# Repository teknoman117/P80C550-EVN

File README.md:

P80C550-EVN (Rev 1.01)
====================

The P80C550-EVN is a small 8051 single board computer designed around the notion of sourcing the major components from the random collection of electronics I've accumulated over the years. It started as a breadboard computer I built after being inspired to resume my electronics hobby after watching Ben Eater's YouTube series. After carting the breadboard computer around enough for the wires to start randomly loosening, I figured I might as well make a proper PCB for the project.

Features
--------
- CPU: P80C550 @ 11.0592 MHz
- 32 KiB ROM
- 32 KiB SRAM
- Expansion Bus
- HD44780 LCD connector
- 8x 8 bit ADC channels (from CPU)
- AM85C30 Dual UART or SDLC controller
- PCF8584 I2C controller
- MC146818 RTC and RAM with battery backup
- Runs off 5V, or 7V to 18V
- Configurable battery saver with CPU interrupt

Revision History
----------------
Revision 1.0
  - First Board Produced
  - Design and/or Production Errors
    - MAX693 RST signal (active-high) is open collector. This was not mentioned in the chip's datasheet, therefore no pull-up was designed into the board. [#1](https://github.com/teknoman117/P80C550-EVN/issues/1)
    - MAX693 ~RST signal (active-low, wired-OR) does not propagate to RST (active-high). Pushing the reset button will reset only the peripherals and not the CPU. [#2](https://github.com/teknoman117/P80C550-EVN/issues/2)

Revision 1.01
  - Disconnects the non-inverted RST signal from the MAX693
  - Add BSS84 P-Channel MOSFET to invert the ~RST signal. The P80C550 has an internal 50k to 300k pulldown resistor and the ~RST signal is current limited, so no additional components are required other than the MOSFET.

The Hardware
============

## Processor

The CPU is a ROM-less CMOS 8051 microcontroller made by Signetics in the late 1980's. The only major differences from the original are that the Signetics part integrates an 8 bit analog to digital converter (with an 8 channel mux on Port 1), a programmable watchdog timer, and is built on a CMOS process. By nature of being ROM-less, the majority of the I/O ports must be used for the external bus interface (Port 2 = A8..15, Port 0 = AD0..7, Port 3.6 and 3.7 are the ~RD and ~WR signals). This is both good and bad, as we must use extra chips to get GPIO functions, but allows us to use far more than the 2K/4K/8K of ROM the 8051 could be ordered with and the 128 bytes of internal RAM. You can also use EEPROM or Flash for code storage, which is much nicer than needing to pick up an EPROM eraser.

## Memory Map

The memory for the board is provided via two 28 pin JEDEC compliant memory sockets supporting up to 32 KiB each. The left socket is for the ROM and the right socket is for the external data memory. Typically, an SRAM would be installed into the data socket, but this could also be a ROM or Flash device (such as AT29Cxx) if memory beyond the 128 byte internal RAM and 50 byte RTC/CMOS RAM is not required. Both sockets are mapped in the lower half of their respective address spaces (ROM in lower 32 KiB of CODE memory and the RAM in the lower 32 KiB of XDATA memory).

The onboard peripherals are mapped in the 8 KiB of address space following the XDATA memory as 1 KiB chunks. This may seem wasteful, but it allows using a single '138 3-to-8 decoder for peripheral chip selects (active high enable is A15, active low enables are A14 and A13. A12 -> A10 are then used for the select input).

| Code Address   | Description |
| -------------- | ----------- |
| 0000h -> 7FFFh | 32 KiB ROM socket (by default - see [Expansion](#expansion)) |
| 8000h -> FFFFh | **unused**  |

| Data Address   | Description                                     |
| -------------- | ----------------------------------------------- |
| 0000h -> 7FFFh | 32 KiB XDATA socket                             |
| 8000h          | [Power Status Register](#power-status-register) |
| 8400h -> 8FFFh | **unused**                                      |
| 9000h -> 903Fh | [RTC](#rtc)                                     |
| 9400h -> 9403h | [UART / SDLC](#uart--sdlc)                      |
| 9800h -> 9801h | [I2C controller](#i2c)                          |
| 9C00h -> 9C01h | [LCD](#lcd)                                     |
| A000h -> FFFFh | **unused**                                      |

## Interrupts

The P80C550 has two external interrupt lines which can either be falling edge triggered or low level triggered. There is an internal pullup resistor on the CPU and peripherals with open collector interrupt outputs can be wire-OR'd together on the same interrupt line.

| Interrupt | Devices                |
| --------- | ---------------------- |
| EX0       | Power Fault, RTC, I2C  |
| EX1       | UART / SDLC            |

## Power and Battery Saver

The board can either be powered directly via the 5V rail, or by a 7V to 18V terminal block, which is regulated to 5V by an AP62150WU-7 buck regulator. The input voltage range means the board can be safely powered by
- 5 to 12 AA(A) batteries
- 6 to 12 cell NiMH batteries
- 2 to 4 cell Li-ion or Li-Poly batteries

There is also a holder for an *optional* CR1216, CR1220, or CR1225 3V coin cell to power the RTC. If omitted, RTC and CMOS state will be lost on power-off. A CR1216 is good for at least 2 months (and counting).

A MAX693 microprocessor supervisor is used to manage the power-on reset delay, the RTC backup power, a low power fault signal, and provide 5V rail undervoltage protection.

A potentiometer is provided to configure the low power threshold. A jumper ("PFI Input Select") is provided to select whether the source voltage is provided from the Vin terminal block or the 5V rail. The former is used in battery powered or other scenarios using the input regulator and the latter is used when the 5V rail is directly driven. A 5.1V zener diode protects from accidental overvoltage on the voltage reference inputs.

The MAX693 will report a low power fault when the reference input drops below **1.3V**. By default, this will trigger the EX0 interrupt on the P80C550. A single bit register ([Power Status Register](#power-status-register)) is provided to check the status of the power fault output of the MAX693 and to mask the interrupt it generates.

For scenarios directly powering the 5V rail, the voltage divider should be configured to output 1.444V at 5V. This will trigger the lower power fault if the rail drops to 4.5V, which is the minimum safe CPU operating voltage. The MAX693 will hold the CPU in a reset state if the 5V rail drops further to 4.4V.

In Vin powered scenarios, the AP62150WU-7 buck regulator will shut down when the reference input drops below **1.2V** and completely cut power to the board. The voltage divider should be configured such that power is cut when the voltage drops to the minimum voltage of your battery, or the minimum voltage of the regulator (about 6.5V).

To determine the output voltage of the voltage divider at a specific input voltage given a target cutoff voltage, use the following formula:

 > Vout = Vin * (1.2V / Vcutoff);

Vin is the current input voltage and Vcutoff is the desired voltage for the regulator to shut off. Vout is the voltage that the voltage divider should be configured to output at that input voltage. See the example configurations below. The emphasis on maximum voltages is to ensure you are aware that "fresh off the charger" batteries have a notably higher voltage than their nominal voltage (which they will drop to quickly), so be aware of this when tuning the cutoff reference.

### Example Voltage Divider Configurations
- Directly powering the 5V rail
  - PFI Input Select: 5V rail
  - Vcutoff = 4.5V (minimum **cpu** voltage)
  - Vout = **5V** * (1.3V / 4.5V) = 1.444V
    - Low Power Fault at 4.5V on 5V rail
    - CPU held in reset at 4.4V on 5V rail

- Li-Ion or Li-Poly Batteries (per cell: 4.2V maximum, 3.7V nominal, and 3.0V minimum)
  - PFI Input Select: Vin
  - 2 cell battery (8.4V maximum, 7.4V nominal, 6V minimum)
    - Vcutoff = 6.5V (minimum **regulator** voltage)
    - Vout = **8.4V** * (1.2V / 6.5V) = 1.550V
    - Vout = **7.4V** * (1.2V / 6.5V) = 1.366V
      - Low Power Fault at 7.04V on Vin (~12% charge)
      - Power cutoff at 6.5V on Vin (~7% charge)
  - 3 cell battery (12.6V maximum, 11.1V nominal, 9V minimum)
    - Vcutoff = 9V (minimum **battery** voltage)
    - Vout = **12.6V** * (1.2V / 9V) = 1.680V
    - Vout = **11.1V** * (1.2V / 9V) = 1.480V
      - Low Power Fault at 9.75V on Vin (~7% charge)
      - Power cutoff at 9V on Vin (~5% charge)
  - 4 cell battery (16.8V maximum, 14.8V nominal, 12V minimum)
    - Vcutoff = 12V (minimum **battery** voltage)
    - Vout = **16.8V** * (1.2V / 12V) = 1.680V
    - Vout = **14.8V** * (1.2V / 12V) = 1.480V
      - Low Power Fault at 13V on Vin (~7% charge)
      - Power cutoff at 12V on Vin (~5% charge)

- NiMH Batteries (per cell: 1.5V maximum, 1.2V nominal, and 1.0V minimum)
  - PFI Input Select: Vin
  - 7 cell battery (10.5V maximum, 8.4V nominal, 7.0V minimum)
    - Vcutoff = 7V (minimum **battery** voltage)
    - Vout = **10.5V** * (1.2 / 7V) = 1.800V
    - Vout = **8.4V** * (1.2 / 7V) = 1.440V
      - Low Power Fault at 7.58V on Vin (~5% charge)
      - Power cuttoff at 7V on Vin (~0% charge)

### Power Status Register
- Address: 8000h
- Read: Bit 7 is the ~PFO (Power Fault) line from the MAX 693 Supervisor
  - 0 = Low Voltage
  - 1 = Nominal Voltage
- Write: Bit 7 is the ~PFO (Power Fault) interrupt mask
  - 0 = Enable PFO interrupt
  - 1 = Disable PFO interrupt
- Bits 0 -> 6 undefined

## UART / SDLC

The AM85C30 "Enhanced Serial Communications Controller" can function as a UART or as an SDLC/HDLC controller. In UART mode, there is a 3 byte RX FIFO, but no TX FIFO. The SDLC/HDLC mode adds a 10 entry frame status FIFO, but the data FIFOs remain the same. The chip is intended to be used with a DMA engine, but this does not exist on the 8051 platform. If a deeper FIFO is required, there is a more modern (less old?) drop-in compatible version available called the Z85230, which appears to still in production. It adds a 4 byte TX FIFO and increases the RX FIFO to 8 bytes from 3 bytes.

| Data Address | Description         |
| ------------ | ------------------- |
| 9400h        | Channel B - Control |
| 9401h        | Channel B - Data    |
| 9402h        | Channel A - Control |
| 9403h        | Channel A - Data    |

## I2C

The PCF8584 is an I2C controller supporting a 100 KHz SCL frequency in either master or slave mode.

| Data Address | Description      |
| ------------ | ---------------- |
| 9800h        | Register Access  |
| 9801h        | Control          |

## RTC

The RTC is the classic MC146818 chip that was present in the PC/AT that defined the pinout and register layout that later parts such as the Dallas DS1285, DS12885, and DS1685 use. No special battery input, no integrated oscillator, etc. The MAX693 is used to avoid needing the diode setup specified in the manual. 

| Data Address   | Description                    |
| -------------- | ------------------------------ |
| 9000h          | Seconds                        |
| 9001h          | Seconds (Alarm)                |
| 9002h          | Minutes                        |
| 9003h          | Minutes (Alarm)                |
| 9004h          | Hours                          |
| 9005h          | Hours (Alarm)                  |
| 9006h          | Day of Week                    |
| 9007h          | Day of Month                   |
| 9008h          | Month                          |
| 9009h          | Year                           |
| 900Ah          | Register A                     |
| 900Bh          | Register B                     |
| 900Ch          | Register C                     |
| 900Dh          | Register D                     |
| 900Eh -> 903Fh | 50 bytes of Battery Backed RAM |

## LCD

Any LCD module compatible with the 16 pin HD44780 header may be used. The mounting holes are spaced for the popular LCD2004A module (20x4 characters) that can be found pretty much everywhere.

| Data Address | Description   |
| ------------ | ------------- |
| 9C00h        | LCD - Control |
| 9C01h        | LCD - Data    |

## PCB
| Front Side | Back Side |
| ---------- | --------- |
|  |  |

| Layout (Power Planes Not Shown) |
| ---------------------------------- |
|  |

The PCB is a 98 mm by 69 mm, 4-layer board (2 signal layers, one +5V plane, and one ground plane) following the design rules for the low cost JLCPCB 4-layer process. Using 4 layers made the routing far easier, as I didn't have to worry about getting power in and around all of the signal traces. At time time of writing, 5 boards using Leaded HASL and a green PCB material is $8 (USD). Switching to ENIG-RoHS increases the price to $23.40 (USD) for 5 boards. 10 boards is $29 (USD), as they seemingly charge a flat rate for switching to ENIG on small orders. I also opted for FR4 TG155 because it's more tolerant to hot air soldering.

To order, you can contact me at [hardware@nrlewis.dev](mailto:hardware@nrlewis.dev) and see if I have any laying around, or you can send the gerber files (attached to release tags) to your board house of choice. JLCPCB is my recommendation, as it seems that they have a lower 4-layer board tier available. PCBWay seems good as well, but their 4-layer process is a bit overkill for this board.

The smallest components on the PCB are 0603 passives. These are the smallest size I'm comfortable hand soldering. Call me crazy, but I assembled this whole board using a Weller WE1010NA soldering station with a (small point) chisel tip, flux core solder, a flux pen, some solder wick, and a pair of tweezers from an iFixit kit. Apply flux generously, hold the components onto the pads with tweezers, hold your breath, and apply solder.

## Expansion

All of the major bus signals are broken out to stackable headers to allow for stacked expansion boards.

### ROM Expansion

The ROM read signal (~CODE_RD) and chip select (~CODE_CS) are broken out to the address low-byte header. The ~CODE_CS pin has a pulldown to keep the ROM enabled when no expansion boards are installed. The main idea behind these signals is to enable the creation of a self-programming expansion. By default, the ROM socket occupies both the lower and upper 32 KiB of the code address space, as the chip select is always enabled and A15 is ignored. A self programming module would allow the onboard ROM be either relocated or disabled when switching to an external memory.

#### Address Low-Byte Header

| Pin | Description |
| --- | ----------- |
| 1   | GND         |
| 2   | +5V         |
| 3   | A0          |
| 4   | A1          |
| 5   | A2          |
| 6   | A3          |
| 7   | A4          |
| 8   | A5          |
| 9   | A6          |
| 10  | A7          |
| 11  | ~CODE_RD    |
| 12  | ~CODE_CS    |
| 13  | ~RST        |

#### Address High-Byte Header

| Pin | Description |
| --- | ----------- |
| 1   | A15         |
| 2   | A14         |
| 3   | A13         |
| 4   | A12         |
| 5   | A11         |
| 6   | A10         |
| 7   | A9          |
| 8   | A8          |
| 9   | ~WR         |
| 10  | ~RD         |
| 11  | +5V         |
| 12  | GND         |

#### LCD Header

| Pin | Description  |
| --- | ------------ |
| 1   | GND          |
| 2   | +5V          |
| 3   | LCD_VO       |
| 4   | A0           |
| 5   | ~WR          |
| 6   | LCD_E        |
| 7   | D0           |
| 8   | D1           |
| 9   | D2           |
| 10  | D3           |
| 11  | D4           |
| 12  | D5           |
| 13  | D6           |
| 14  | D7           |
| 15  | LCD_A (+5V)  |
| 16  | LCD_K        |

#### CPU Peripheral Header

| Pin | Description       |
| --- | ----------------- |
| 1   | UART_IEO          |
| 2   | CLK (11.0592 MHz) |
| 3   | P3.4 - T0         |
| 4   | P3.5 - T1         |
| 5   | P3.3 - ~INT1      |
| 6   | P3.2 - ~INT0      |
| 7   | P3.1 - TxD        |
| 8   | P3.0 - RxD        |
| 9   | +5V               |
| 10  | GND               |

#### ADC Header

| Pin | Description  |
| --- | ------------ |
| 1   | P1.0 (ADC 0) |
| 2   | P1.1 (ADC 1) |
| 3   | P1.2 (ADC 2) |
| 4   | P1.3 (ADC 3) |
| 5   | P1.4 (ADC 4) |
| 6   | P1.5 (ADC 5) |
| 7   | P1.6 (ADC 6) |
| 8   | P1.7 (ADC 7) |

#### UART Headers

| Pin | Description |
| --- | ----------- |
| 1   | DCD         |
| 2   | CTS         |
| 3   | RTS         |
| 4   | DTR         |
| 5   | TX          |
| 6   | TX Clock    |
| 7   | RX          |
| 8   | RX Clock    |
| 9   | SYNC        |
| 10  | REQ         |
| 11  | GND         |
| 12  | +5V         |

## Datasheets

[P80C550EBAA - DigChip](https://www.digchip.com/datasheets/download_datasheet.php?id=741162&part-number=P80C550EBAA)

[MAX693 - Maxim](https://datasheets.maximintegrated.com/en/ds/MAX690-MAX695.pdf)

[AM85C30 (1) - ChipDB](http://datasheets.chipdb.org/AMD/07513.pdf)

[AM85C30 (2) - Rockby](https://www.rockby.com.au/DSheets/26719.pdf)

[PCF8584 - NXP](https://www.nxp.com/docs/en/data-sheet/PCF8584.pdf)

[MC146818 - NXP](https://www.nxp.com/docs/en/data-sheet/MC146818.pdf)

[LCD2004A - Beta-eStore](https://www.beta-estore.com/download/rk/RK-10290_410.pdf)

## Background

The design goal was for the major components to be sourced from the collection of random electronics I've accumulated over the years - hence a board built around archaic parts newly created in 2021.

The peripherals are straight out of a 1980's PC builder's kit. I think it was 2003 when I received the core parts of this board. I was a member of Chibots in Chicago as a kid and I picked them up during the regular "I'm not taking this back home with me" parts dump / swap meet at the end of club meetings. I ended up with a tubes of 8051 controllers, MAX693 microprocessor supervisors, AM85C30 Dual UARTs / SDLC / HDLC controllers, MC146818 RTC/RAMs (used on PC/AT), and some engineering sample RS232 to TTL level shifters (XC prefix Motorola parts). I have to imagine the person who gave them to me had to have built a board along these lines sometime in the past. Probably with these components. I bet they didn't have the luxury of dirt-cheap 4 layer PCBs though and open source EDA tools :).

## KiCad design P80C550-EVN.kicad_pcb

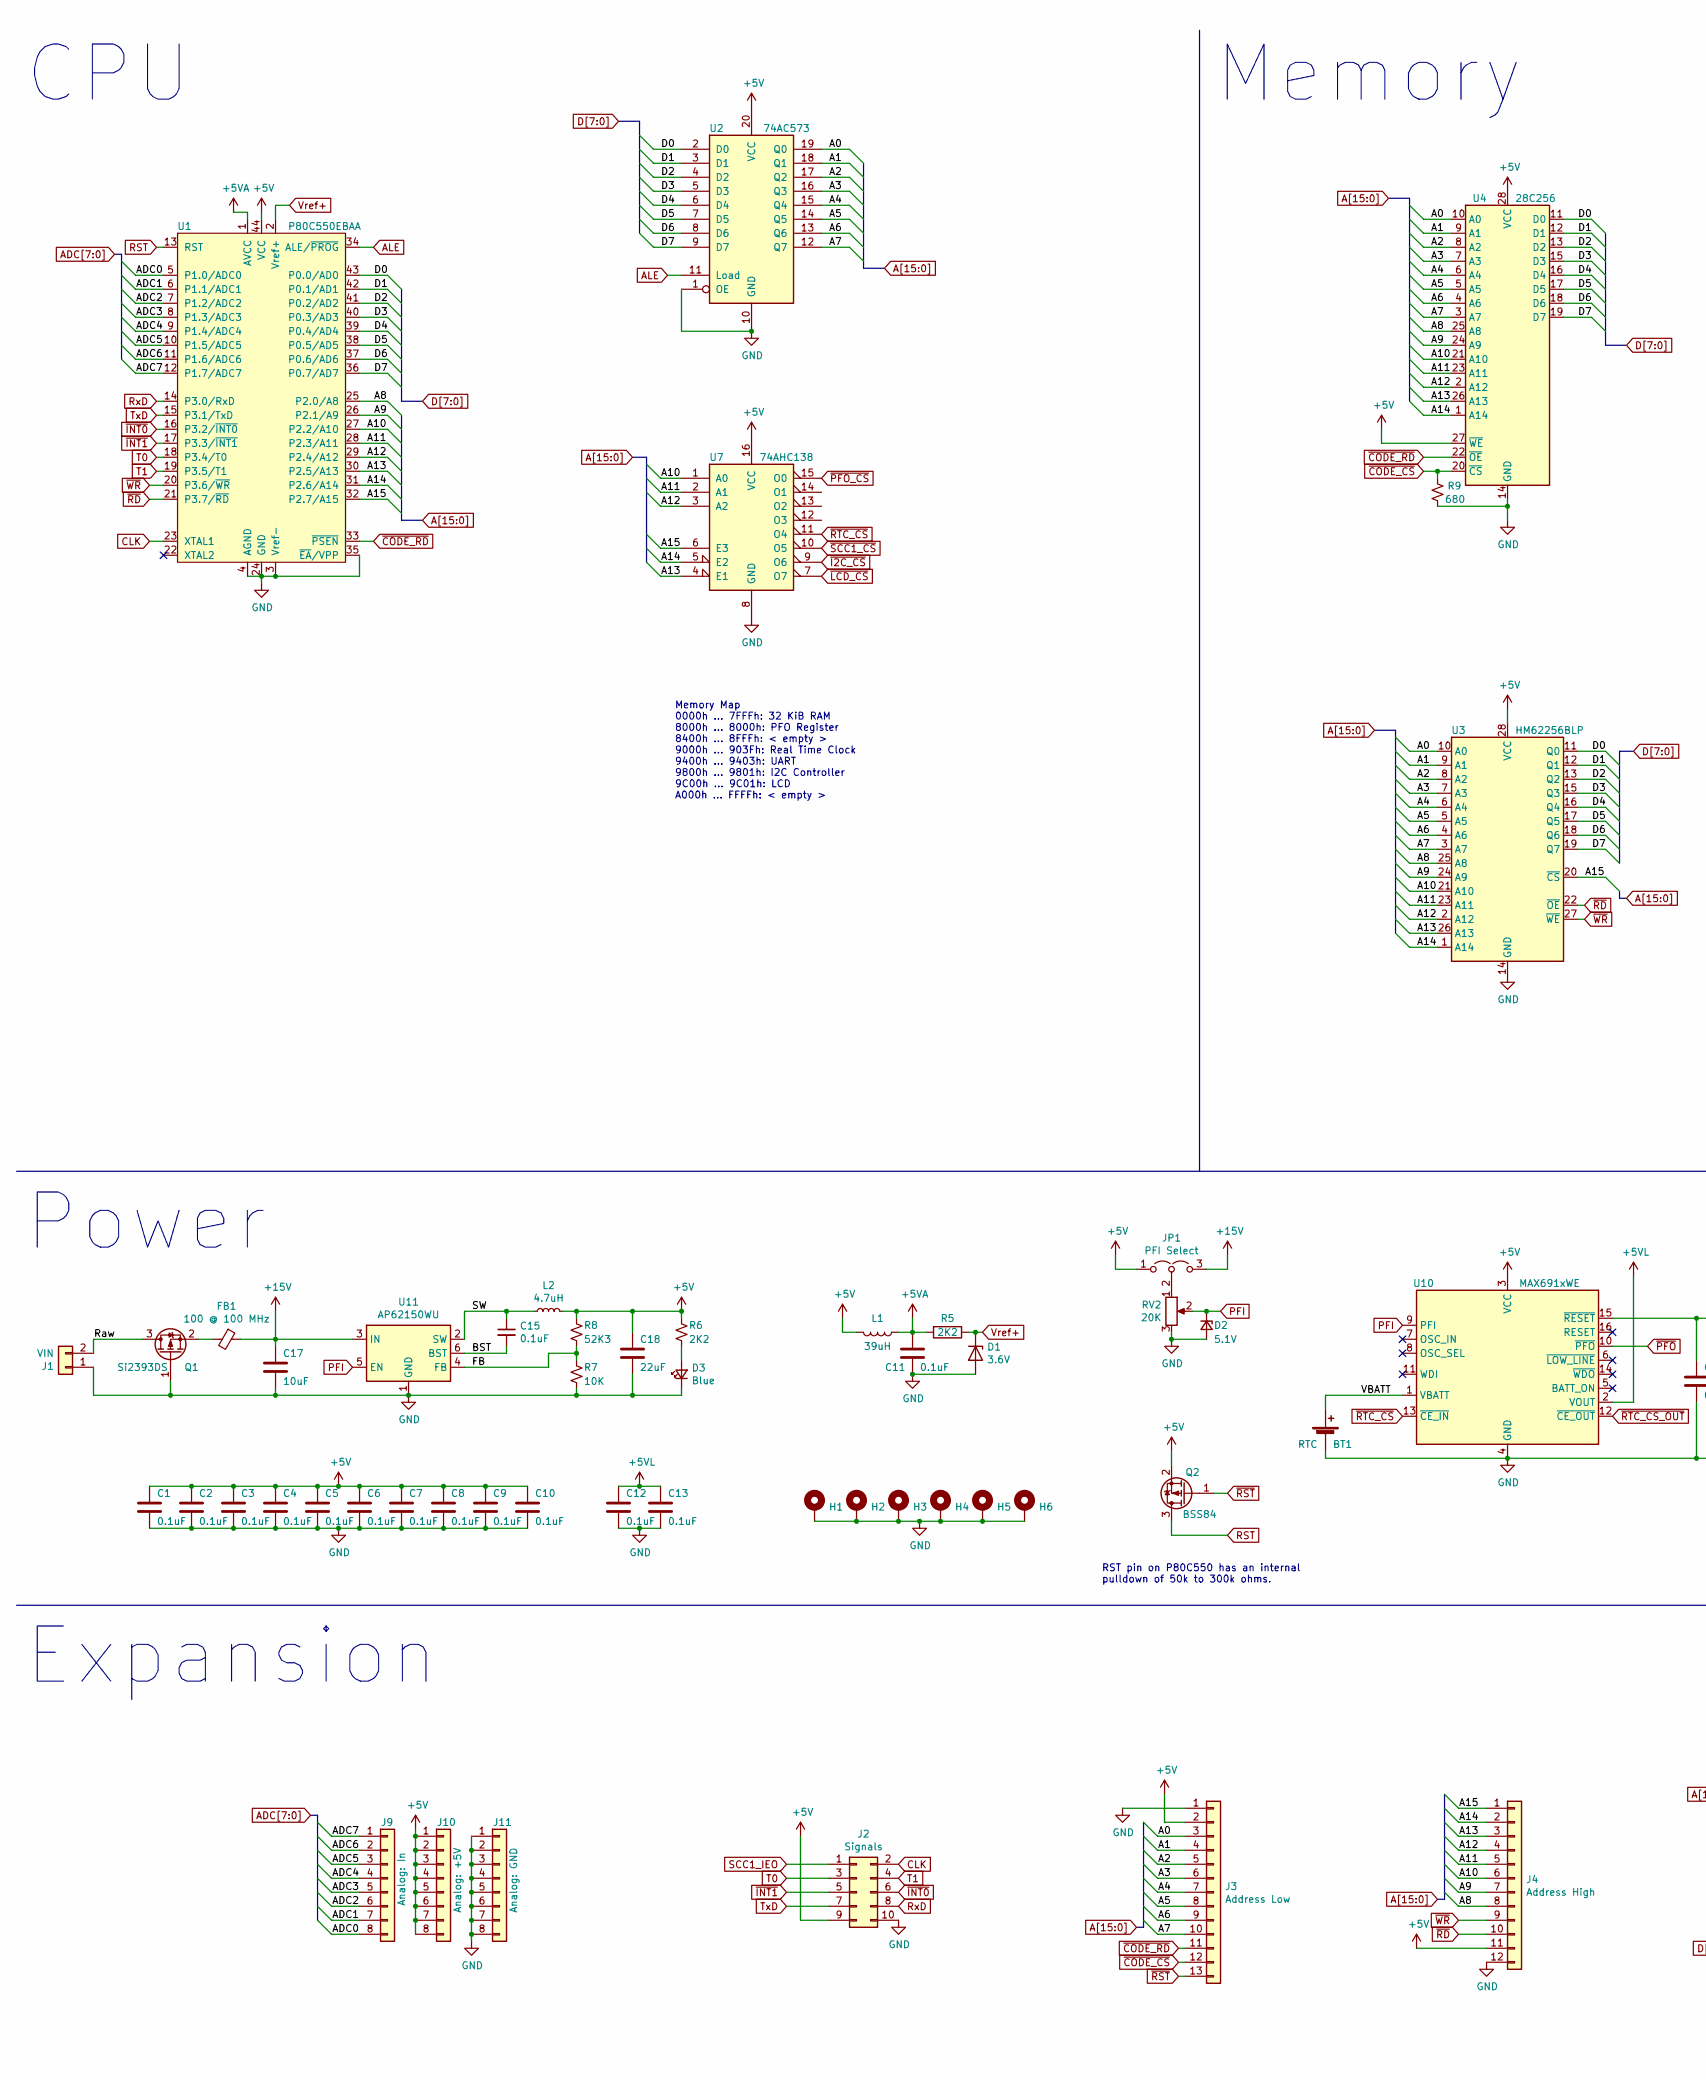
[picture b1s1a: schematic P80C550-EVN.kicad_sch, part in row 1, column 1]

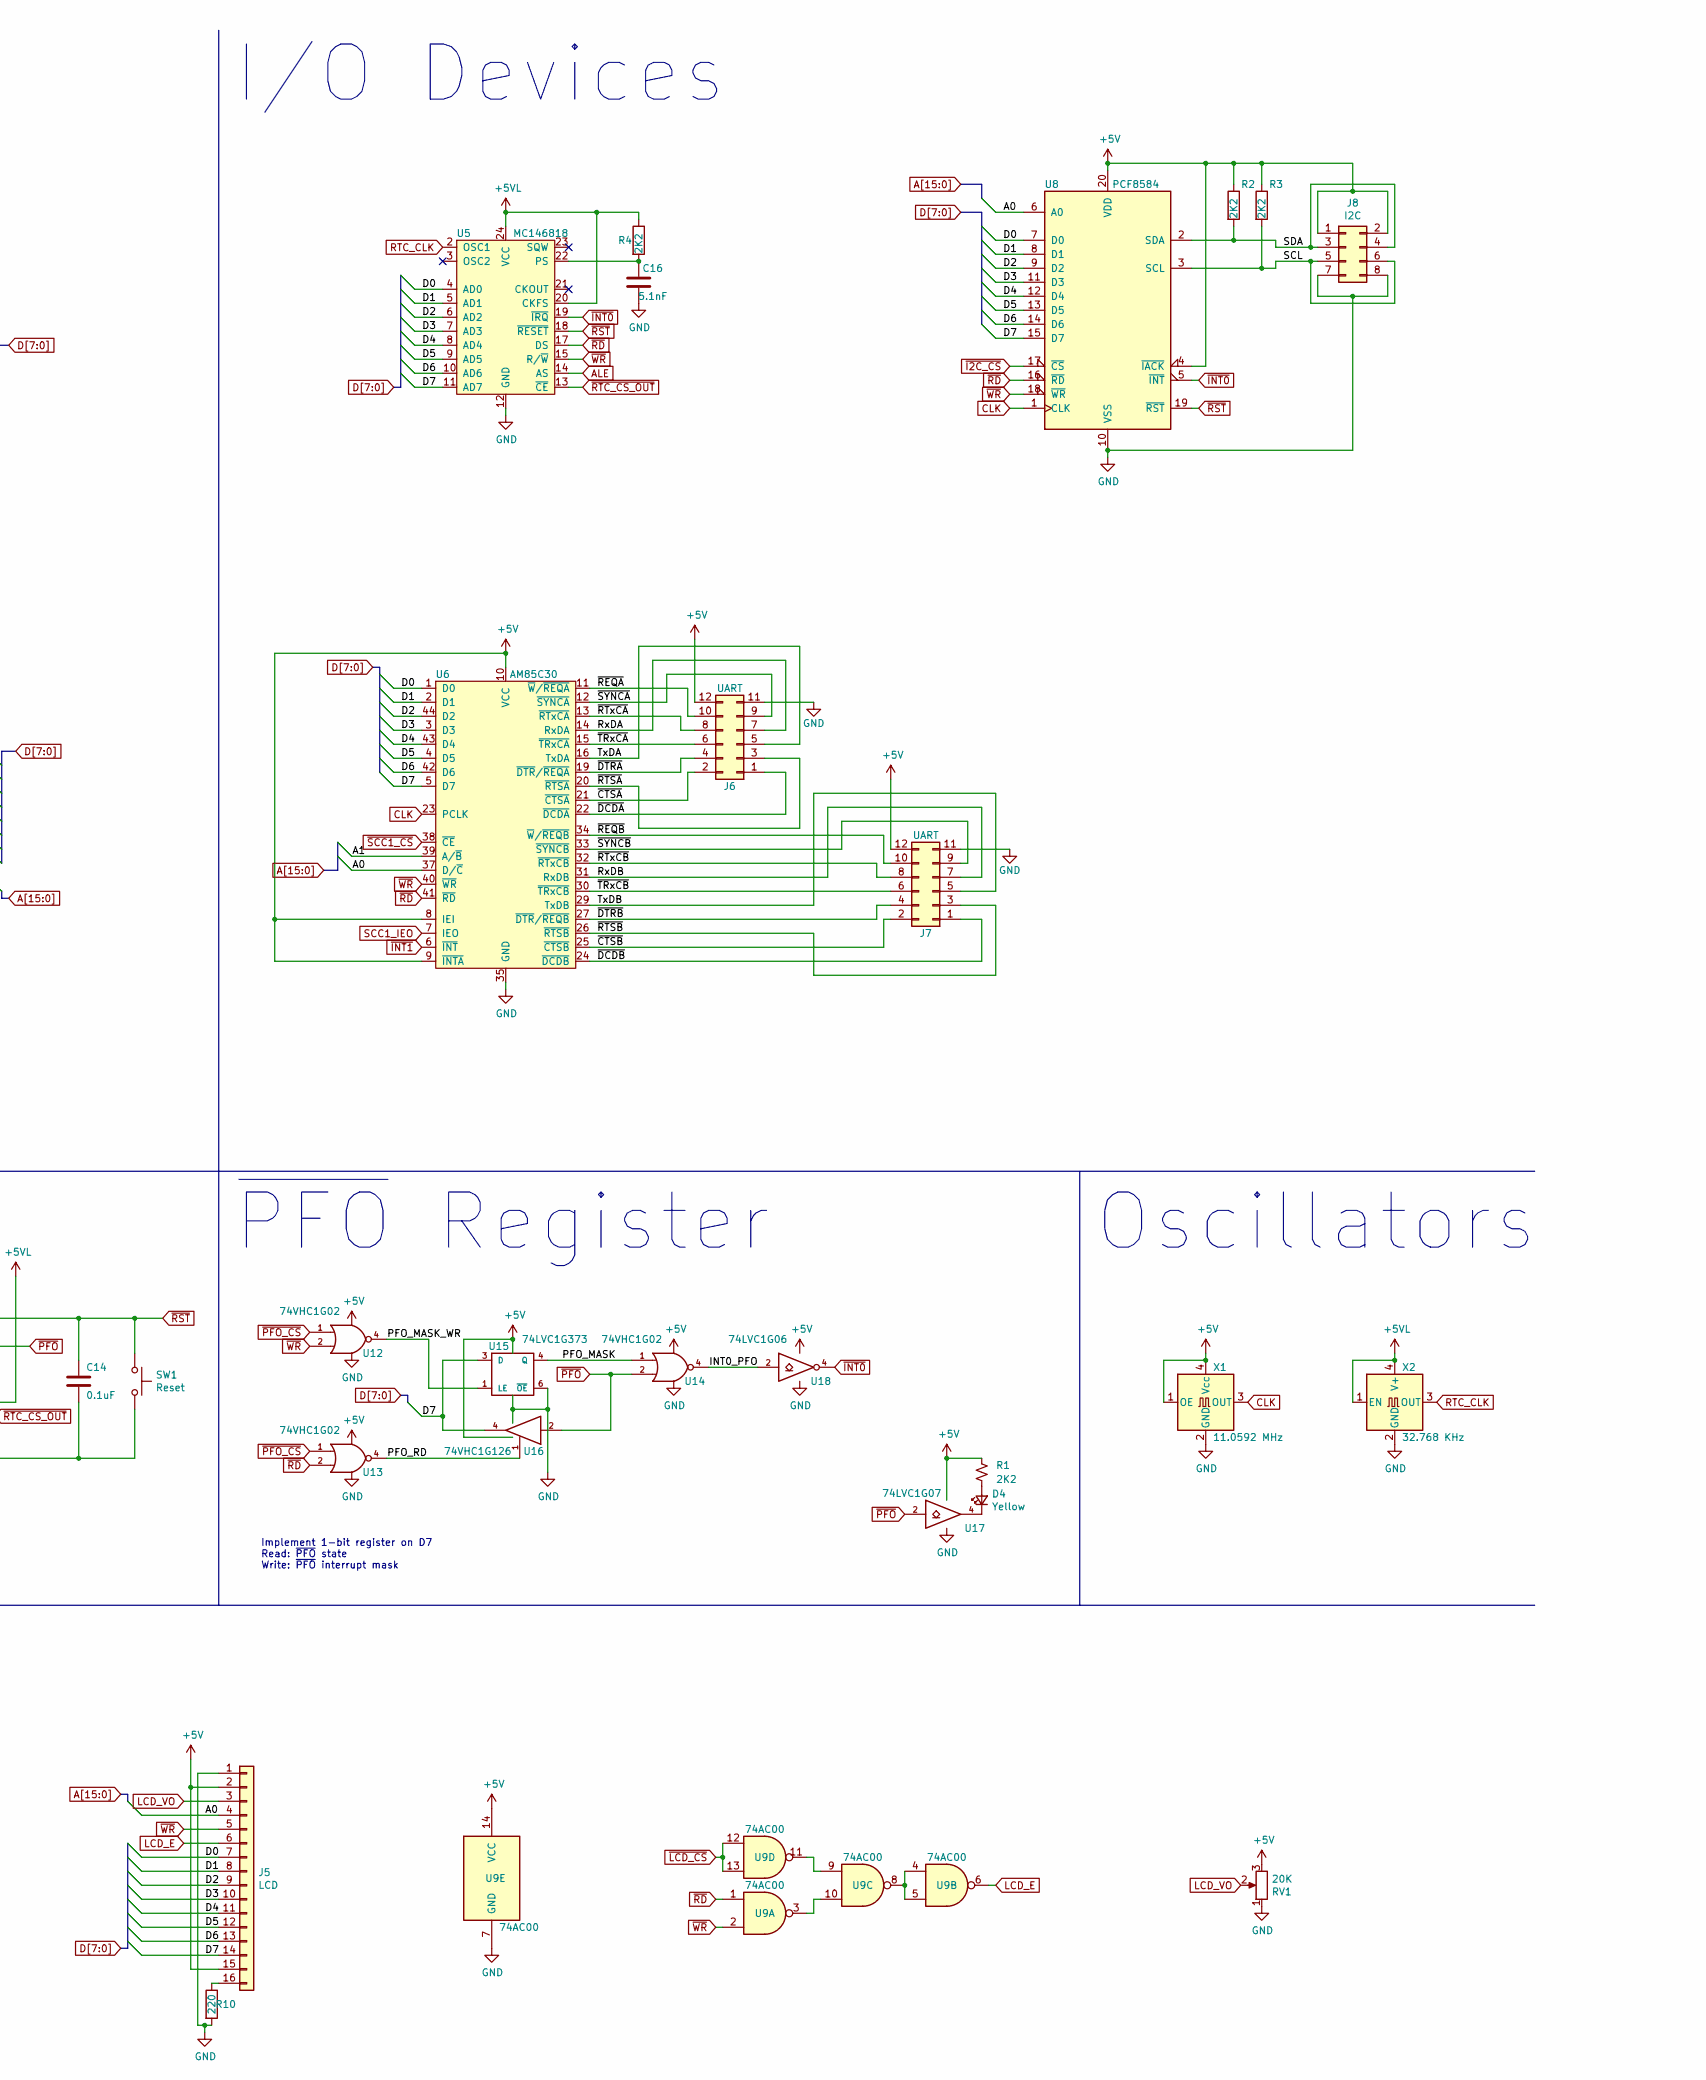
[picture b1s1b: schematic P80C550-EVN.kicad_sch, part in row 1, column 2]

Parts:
BT1: RTC; BatteryHolder_Keystone_3001_1x12mm; Manufacturer_PN 3001; Digikey_PN 36-3001-ND‎
C1, C2, C3, C4, C5, C6, C7, C8, C9, C10, C11, C12, C13, C14, C15: 0.1uF; C_0603_1608Metric_Pad1.08x0.95mm_HandSolder; Manufacturer_PN C1608X7R1E104K080AA; Digikey_PN 445-1316-1-ND‎
C16: 5.1nF; C_0603_1608Metric_Pad1.08x0.95mm_HandSolder; Manufacturer_PN 06033C512JAT4A; Digikey_PN 478-06033C512JAT4ACT-ND
C17: 10uF; C_0805_2012Metric_Pad1.18x1.45mm_HandSolder; Manufacturer_PN TMK212BBJ106KG-T; Digikey_PN 587-2985-1-ND
C18: 22uF; C_0805_2012Metric_Pad1.18x1.45mm_HandSolder; Manufacturer_PN LMK212BBJ226MG-T; Digikey_PN 587-5464-1-ND
D1: 3.6V; D_SOT-23_ANK; Manufacturer_PN BZX84-C3V6,215; Digikey_PN 1727-5033-1-ND‎
D2: 5.1V; D_SOT-23_ANK; Manufacturer_PN BZX84-C5V1,235; Digikey_PN 1727-2130-1-ND‎
D3: Blue; LED_0603_1608Metric_Pad1.05x0.95mm_HandSolder; Manufacturer_PN IN-S63BT5B; Digikey_PN ‎1830-1068-1-ND‎
D4: Yellow; LED_0603_1608Metric_Pad1.05x0.95mm_HandSolder; Manufacturer_PN IN-S63BTR; Digikey_PN 1830-1072-1-ND‎
FB1: 100 @ 100 MHz; L_0603_1608Metric_Pad1.05x0.95mm_HandSolder; Manufacturer_PN FBMH1608HM101-T; Digikey_PN 587-1738-1-ND‎
H1, H2, H3, H4, H5, H6: MountingHole_Pad; MountingHole_3.5mm_Pad_LCD
J1: VIN; TerminalBlock_bornier-2_P5.08mm; Manufacturer_PN 34.102; Digikey_PN 1920-1323-ND
J2: Signals; PinSocket_2x05_P2.54mm_Vertical; Manufacturer_PN PPPC052LFBN-RC; Digikey_PN S7108-ND
J3: Address Low; PinSocket_1x13_P2.54mm_Vertical; Manufacturer_PN PPPC131LFBN-RC; Digikey_PN S7046-ND
J4: Address High; PinSocket_1x12_P2.54mm_Vertical; Manufacturer_PN PPPC131LFBN-RC; Digikey_PN S7046-ND
J5: LCD; PinSocket_1x16_P2.54mm_Vertical; Manufacturer_PN PPPC161LFBN-RC; Digikey_PN S7049-ND
J6, J7: UART; PinHeader_2x06_P2.54mm_Horizontal; Manufacturer_PN PRPC006DBAN-M71RC; Digikey_PN S2111EC-06-ND
J8: I2C; PinHeader_2x04_P2.54mm_Vertical; Manufacturer_PN PRPC004DAAN-RC; Digikey_PN S2011EC-04-ND
J9: Analog: In; PinHeader_1x08_P2.54mm_Vertical; Manufacturer_PN PRPC008SAAN-RC; Digikey_PN S1011EC-08-ND
J10: Analog: +5V; PinHeader_1x08_P2.54mm_Vertical; Manufacturer_PN PRPC008SAAN-RC; Digikey_PN S1011EC-08-ND
J11: Analog: GND; PinHeader_1x08_P2.54mm_Vertical; Manufacturer_PN PRPC008SAAN-RC; Digikey_PN S1011EC-08-ND
JP1: PFI Select; PinHeader_1x03_P1.27mm_Vertical_SMD_Pin1Left; Manufacturer_PN M50-3630342; Digikey_PN 952-3607-ND
L1: 39uH; L_0603_1608Metric_Pad1.05x0.95mm_HandSolder; Manufacturer_PN L-14C39NJV4T; Digikey_PN 712-1441-1-ND‎
L2: 4.7uH; L_1008_2520Metric_Pad1.43x2.20mm_HandSolder; Manufacturer_PN AIML-1008HC-4R7M-T; Digikey_PN 535-12797-1-ND
Q1: Si2393DS; SOT-23; Manufacturer_PN SI2393DS-T1-GE3; Digikey_PN ‎742-SI2393DS-T1-GE3CT-ND‎
Q2: BSS84; SOT-23; Manufacturer_PN BSS84; Digikey_PN BSS84CT-ND
R1, R2, R3, R4, R5, R6: 2K2; R_0603_1608Metric_Pad0.98x0.95mm_HandSolder; Manufacturer_PN CR0603-FX-2201ELF; Digikey_PN 118-CR0603-FX-2201ELFCT-ND‎
R7: 10K; R_0603_1608Metric_Pad0.98x0.95mm_HandSolder; Manufacturer_PN CR0603-FX-1002ELF; Digikey_PN CR0603-FX-1002ELFCT-ND
R8: 52K3; R_0603_1608Metric_Pad0.98x0.95mm_HandSolder; Manufacturer_PN CR0603-FX-5232ELF; Digikey_PN CR0603-FX-5232ELFCT-ND
R9: 680; R_0603_1608Metric_Pad0.98x0.95mm_HandSolder; Manufacturer_PN CR0603-JW-681ELF; Digikey_PN 118-CR0603-JW-681ELFCT-ND‎
R10: 220; R_Axial_DIN0207_L6.3mm_D2.5mm_P7.62mm_Horizontal
RV1, RV2: 20K; Potentiometer_Bourns_TC33X_Vertical; Manufacturer_PN TC33X-1-203E; Digikey_PN TC33X-1-203ECT-ND
SW1: Reset; SW_Tactile_SPST_Angled_PTS645Vx39-2LFS; Manufacturer_PN PTS645VM39-2 LFS; Digikey_PN CKN10909-ND
U1: P80C550EBAA; PLCC-44_THT-Socket
U2: 74AC573; DIP-20_W7.62mm_Socket; Manufacturer_PN CD74AC573E; Digikey_PN 296-1379-5-ND
U3: HM62256BLP; DIP-28_W15.24mm_Socket; Manufacturer_PN AS6C62256-55PCN; Digikey_PN AS6C62256-55PCN
U4: 28C256; DIP-28_W15.24mm_Socket; Manufacturer_PN AT28C256-15PU; Digikey_PN AT28C256-15PU-ND
U5: MC146818; DIP-24_W15.24mm_Socket
U6: AM85C30; PLCC-44_THT-Socket; Manufacturer_PN Z8523016VSG; Digikey_PN 269-3927-ND
U7: 74AHC138; DIP-16_W7.62mm_Socket; Manufacturer_PN CD74AC138E; Digikey_PN 296-4225-5-ND
U8: PCF8584; DIP-20_W7.62mm_Socket
U9: 74AC00; DIP-14_W7.62mm_Socket; Manufacturer_PN CD74AC00E; Digikey_PN 296-4214-5-ND
U10: MAX691xWE; SOIC-16W_7.5x10.3mm_P1.27mm
U11: AP62150WU; TSOT-23-6; Manufacturer_PN AP62150WU-7; Digikey_PN 31-AP62150WU-7CT-ND
U12, U13, U14: 74VHC1G02; TSOT-23-5_HandSoldering; Manufacturer_PN MC74VHC1G02DTT1G; Digikey_PN MC74VHC1G02DTT1GOSCT-ND‎
U15: 74LVC1G373; SOT-23-6_Handsoldering; Manufacturer_PN SN74LVC1G373DBVR; Digikey_PN 296-18588-1-ND‎
U16: 74VHC1G126; TSOT-23-5_HandSoldering; Manufacturer_PN M74VHC1G126DTT1G; Digikey_PN M74VHC1G126DTT1GOSCT-ND‎
U17: 74LVC1G07; SOT-353_SC-70-5_Handsoldering; Manufacturer_PN 74LVC1G07GW-Q100H; Digikey_PN 1727-1181-1-ND‎
U18: 74LVC1G06; SOT-353_SC-70-5_Handsoldering; Manufacturer_PN 74LVC1G06GW,125; Digikey_PN 1727-6064-1-ND‎
X1: 11.0592 MHz; Oscillator_SMD_SeikoEpson_SG8002CA-4Pin_7.0x5.0mm_HandSolde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; Manufacturer_PN SG7050CCN 11.059200M-HJGA3; Digikey_PN SER4011CT-ND‎
X2: 32.768 KHz; Oscillator_SMD_EuroQuartz_XO32-4Pin_3.2x2.5mm_HandSoldering; Manufacturer_PN ECS-327KE-TR; Digikey_PN XC1751CT-ND‎

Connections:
+5V: C1.1, C2.1, C3.1, C4.1, C5.1, C6.1, C7.1, C8.1, C9.1, C10.1, C18.1, J2.9, J3.2, J4.11, J5.2, J5.15, J6.12, J7.12, J8.1, J8.2, J10.1, J10.2, J10.3, J10.4, J10.5, J10.6, J10.7, J10.8, JP1.1 (A), L1.2, L2.2, Q2.2 (S), R1.1, R2.1, R3.1, R6.1, R8.1, RV1.3, U1.44 (VCC), U2.20 (VCC), U3.28 (VCC), U4.27 (~WE), U4.28 (VCC), U6.8 (IEI), U6.9 (~INTA), U6.10 (VCC), U7.16 (VCC), U8.4 (~IACK), U8.20 (VDD), U9.14 (VCC), U10.3 (VCC), U12.5 (VCC), U13.5 (VCC), U14.5 (VCC), U15.5 (VCC), U16.5 (VCC), U17.5 (VCC), U18.5 (VCC), X1.1 (OE), X1.4 (Vcc)
+5VA: C11.1, L1.1, R5.2, U1.1 (AVCC)
+5VL: C12.1, C13.1, R4.1, U5.20 (CKFS), U5.24 (VCC), U10.2 (VOUT), X2.1 (EN), X2.4 (V+)
+15V: C17.1, FB1.1, JP1.3 (B), U11.3 (IN)
/A0: J3.3, J5.4, U2.19 (Q0), U3.10 (A0), U4.10 (A0), U6.37 (D/~C), U8.6 (A0)
/A1: J3.4, U2.18 (Q1), U3.9 (A1), U4.9 (A1), U6.39 (A/~B)
/A2: J3.5, U2.17 (Q2), U3.8 (A2), U4.8 (A2)
/A3: J3.6, U2.16 (Q3), U3.7 (A3), U4.7 (A3)
/A4: J3.7, U2.15 (Q4), U3.6 (A4), U4.6 (A4)
/A5: J3.8, U2.14 (Q5), U3.5 (A5), U4.5 (A5)
/A6: J3.9, U2.13 (Q6), U3.4 (A6), U4.4 (A6)
/A7: J3.10, U2.12 (Q7), U3.3 (A7), U4.3 (A7)
/A8: J4.8, U1.25 (P2.0/A8), U3.25 (A8), U4.25 (A8)
/A9: J4.7, U1.26 (P2.1/A9), U3.24 (A9), U4.24 (A9)
/A10: J4.6, U1.27 (P2.2/A10), U3.21 (A10), U4.21 (A10), U7.1 (A0)
/A11: J4.5, U1.28 (P2.3/A11), U3.23 (A11), U4.23 (A11), U7.2 (A1)
/A12: J4.4, U1.29 (P2.4/A12), U3.2 (A12), U4.2 (A12), U7.3 (A2)
/A13: J4.3, U1.30 (P2.5/A13), U3.26 (A13), U4.26 (A13), U7.4 (E1)
/A14: J4.2, U1.31 (P2.6/A14), U3.1 (A14), U4.1 (A14), U7.5 (E2)
/A15: J4.1, U1.32 (P2.7/A15), U3.20 (~CS), U7.6 (E3)
/ADC0: J9.8, U1.5 (P1.0/ADC0)
/ADC1: J9.7, U1.6 (P1.1/ADC1)
/ADC2: J9.6, U1.7 (P1.2/ADC2)
/ADC3: J9.5, U1.8 (P1.3/ADC3)
/ADC4: J9.4, U1.9 (P1.4/ADC4)
/ADC5: J9.3, U1.10 (P1.5/ADC5)
/ADC6: J9.2, U1.11 (P1.6/ADC6)
/ADC7: J9.1, U1.12 (P1.7/ADC7)
/BST: C15.2, U11.6 (BST)
/D0: J5.7, U1.43 (P0.0/AD0), U2.2 (D0), U3.11 (Q0), U4.11 (D0), U5.4 (AD0), U6.1 (D0), U8.7 (D0)
/D1: J5.8, U1.42 (P0.1/AD1), U2.3 (D1), U3.12 (Q1), U4.12 (D1), U5.5 (AD1), U6.2 (D1), U8.8 (D1)
/D2: J5.9, U1.41 (P0.2/AD2), U2.4 (D2), U3.13 (Q2), U4.13 (D2), U5.6 (AD2), U6.44 (D2), U8.9 (D2)
/D3: J5.10, U1.40 (P0.3/AD3), U2.5 (D3), U3.15 (Q3), U4.15 (D3), U5.7 (AD3), U6.3 (D3), U8.11 (D3)
/D4: J5.11, U1.39 (P0.4/AD4), U2.6 (D4), U3.16 (Q4), U4.16 (D4), U5.8 (AD4), U6.43 (D4), U8.12 (D4)
/D5: J5.12, U1.38 (P0.5/AD5), U2.7 (D5), U3.17 (Q5), U4.17 (D5), U5.9 (AD5), U6.4 (D5), U8.13 (D5)
/D6: J5.13, U1.37 (P0.6/AD6), U2.8 (D6), U3.18 (Q6), U4.18 (D6), U5.10 (AD6), U6.42 (D6), U8.14 (D6)
/D7: J5.14, U1.36 (P0.7/AD7), U2.9 (D7), U3.19 (Q7), U4.19 (D7), U5.11 (AD7), U6.5 (D7), U8.15 (D7), U15.3 (D), U16.4
/FB: R7.1, R8.2, U11.4 (FB)
/INT0_PFO: U14.4, U18.2
/PFO_MASK: U14.1, U15.4 (Q)
/PFO_MASK_WR: U12.4, U15.1 (LE)
/PFO_RD: U13.4, U16.1
/Raw: J1.2, Q1.3 (D)
/RxDA: J6.7, U6.14 (RxDA)
/RxDB: J7.7, U6.31 (RxDB)
/SCL: J8.5, J8.6, R3.2, U8.3 (SCL)
/SDA: J8.3, J8.4, R2.2, U8.2 (SDA)
/SW: C15.1, L2.1, U11.2 (SW)
/TxDA: J6.5, U6.16 (TxDA)
/TxDB: J7.5, U6.29 (TxDB)
/VBATT: BT1.1 (+), U10.1 (VBATT)
/~CTSA: J6.2, U6.21 (~CTSA)
/~CTSB: J7.2, U6.25 (~CTSB)
/~DCDA: J6.1, U6.22 (~DCDA)
/~DCDB: J7.1, U6.24 (~DCDB)
/~DTRA: J6.4, U6.19 (~DTR/~REQA)
/~DTRB: J7.4, U6.27 (~DTR/~REQB)
/~REQA: J6.10, U6.11 (~W/~REQA)
/~REQB: J7.10, U6.34 (~W/~REQB)
/~RTSA: J6.3, U6.20 (~RTSA)
/~RTSB: J7.3, U6.26 (~RTSB)
/~RTxCA: J6.8, U6.13 (~RTxCA)
/~RTxCB: J7.8, U6.32 (~RTxCB)
/~SYNCA: J6.9, U6.12 (~SYNCA)
/~SYNCB: J7.9, U6.33 (~SYNCB)
/~TRxCA: J6.6, U6.15 (~TRxCA)
/~TRxCB: J7.6, U6.30 (~TRxCB)
ALE: U1.34 (ALE/~PROG), U2.11 (Load), U5.14 (AS)
CLK: J2.2, U1.23 (XTAL1), U6.23 (PCLK), U8.1 (CLK), X1.3 (OUT)
GND: BT1.2 (-), C1.2, C2.2, C3.2, C4.2, C5.2, C6.2, C7.2, C8.2, C9.2, C10.2, C11.2, C12.2, C13.2, C14.2, C16.1, C17.2, C18.2, D1.2 (A), D2.2 (A), D3.1 (K), H1.1, H2.1, H3.1, H4.1, H5.1, H6.1, J1.1, J2.10, J3.1, J4.12, J5.1, J6.11, J7.11, J8.7, J8.8, J11.1, J11.2, J11.3, J11.4, J11.5, J11.6, J11.7, J11.8, Q1.1 (G), R7.2, R9.2, R10.2, RV1.1, RV2.3, SW1.2, U1.3 (Vref-), U1.4 (AGND), U1.24 (GND), U1.35 (~EA/VPP), U2.1 (OE), U2.10 (GND), U3.14 (GND), U4.14 (GND), U5.12 (GND), U6.35 (GND), U7.8 (GND), U8.10 (VSS), U9.7 (GND), U10.4 (GND), U11.1 (GND), U12.3 (GND), U13.3 (GND), U14.3 (GND), U15.2 (GND), U15.6 (~OE), U16.3 (GND), U17.3 (GND), U18.3 (GND), X1.2 (GND), X2.2 (GND)
LCD_E: J5.6, U9.6
LCD_VO: J5.3, RV1.2
unnamed: C16.2, R4.2, U5.22 (PS)
unnamed: D3.2 (A), R6.2
unnamed: D4.1 (K), U17.4
unnamed: D4.2 (A), R1.2
unnamed: FB1.2, Q1.2 (S)
unnamed: J5.16, R10.1
unnamed: JP1.2 (C), RV2.1
unnamed: U9.4, U9.5, U9.8
unnamed: U9.3, U9.10
unnamed: U9.9, U9.11
PFI: D2.1 (K), RV2.2, U10.9 (PFI), U11.5 (EN)
RST: Q2.3 (D), U1.13 (RST)
RTC_CLK: U5.2 (OSC1), X2.3 (OUT)
RxD: J2.8, U1.14 (P3.0/RxD)
SCC1_IEO: J2.1, U6.7 (IEO)
T0: J2.3, U1.18 (P3.4/T0)
T1: J2.4, U1.19 (P3.5/T1)
TxD: J2.7, U1.15 (P3.1/TxD)
Vref+: D1.1 (K), R5.1, U1.2 (Vref+)
~CODE_CS: J3.12, R9.1, U4.20 (~CS)
~CODE_RD: J3.11, U1.33 (~PSEN), U4.22 (~OE)
~I2C_CS: U7.9 (O6), U8.17 (~CS)
~INT0: J2.6, U1.16 (P3.2/~INT0), U5.19 (~IRQ), U8.5 (~INT), U18.4
~INT1: J2.5, U1.17 (P3.3/~INT1), U6.6 (~INT)
~LCD_CS: U7.7 (O7), U9.12, U9.13
~PFO_CS: U7.15 (O0), U12.1, U13.1
~PFO: U10.10 (~PFO), U14.2, U16.2, U17.2
~RD: J4.10, U1.21 (P3.7/~RD), U3.22 (~OE), U5.17 (DS), U6.41 (~RD), U8.16 (~RD), U9.1, U13.2
~RST: C14.1, J3.13, Q2.1 (G), SW1.1, U5.18 (~RESET), U8.19 (~RST), U10.15 (~RESET)
~RTC_CS_OUT: U5.13 (~CE), U10.12 (~CE_OUT)
~RTC_CS: U7.11 (O4), U10.13 (~CE_IN)
~SCC1_CS: U6.38 (~CE), U7.10 (O5)
~WR: J4.9, J5.5, U1.20 (P3.6/~WR), U3.27 (~WE), U5.15 (R/~W), U6.40 (~WR), U8.18 (~WR), U9.2, U12.2

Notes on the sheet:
Memory
Memory Map 0000h ... 7FFFh: 32 KiB RAM 8000h ... 8000h: PFO Register 8400h ... 8FFFh: < empty > 9000h ... 903Fh: Real Time Clock 9400h ... 9403h: UART 9800h ... 9801h: I2C Controller 9C00h ... 9C01h: LCD A000h ... FFFFh: < empty >
CPU
RST pin on P80C550 has an internal pulldown of 50k to 300k ohms.
Oscillators
~{PFO} Register
I/O Devices
Implement 1-bit register on D7 Read: ~{PFO} state Write: ~{PFO} interrupt mask
Power
Expansion
